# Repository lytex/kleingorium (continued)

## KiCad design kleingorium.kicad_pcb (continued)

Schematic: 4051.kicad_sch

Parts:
C20: 100nF; C_0805_2012Metric
R34, R35, R36, R37: 100k; R_0805_2012Metric
U12: 4051; SOIC-16_3.9x9.9mm_P1.27mm

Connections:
/Bottom plate/4051/A: R35.1, U12.11 (A); also elsewhere on the board
/Bottom plate/4051/B: R36.1, U12.10 (B); also elsewhere on the board
/Bottom plate/4051/C: R37.1, U12.9 (C); also elsewhere on the board
/Bottom plate/4051/Inhibit: R34.1, U12.6 (Inh); also elsewhere on the board
/Bottom plate/4051/X: U12.3 (X)
/Bottom plate/4051/X0: U12.13 (X0); also elsewhere on the board
/Bottom plate/4051/X1: U12.14 (X1); also elsewhere on the board
/Bottom plate/4051/X2: U12.15 (X2); also elsewhere on the board
/Bottom plate/4051/X3: U12.12 (X3); also elsewhere on the board
/Bottom plate/4051/X4: U12.1 (X4); also elsewhere on the board
/Bottom plate/4051/X5: U12.5 (X5); also elsewhere on the board
/Bottom plate/4051/X6: U12.2 (X6); also elsewhere on the board
/Bottom plate/4051/X7: U12.4 (X7); also elsewhere on the board
GND2: C20.2, R34.2, R35.2, R36.2, R37.2, U12.7 (VEE), U12.8 (VSS); also elsewhere on the board
VDDF: C20.1, U12.16 (VDD); also elsewhere on the board

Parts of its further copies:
C22: 100nF; C_0805_2012Metric
R38, R39, R40, R41: 100k; R_0805_2012Metric
U13: 4051; SOIC-16_3.9x9.9mm_P1.27mm

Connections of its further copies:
/Bottom plate/4051 2/A: R39.1, U13.11 (A); also elsewhere on the board
/Bottom plate/4051 2/B: R40.1, U13.10 (B); also elsewhere on the board
/Bottom plate/4051 2/C: R41.1, U13.9 (C); also elsewhere on the board
/Bottom plate/4051 2/Inhibit: R38.1, U13.6 (Inh); also elsewhere on the board
/Bottom plate/4051 2/X: U13.3 (X); also elsewhere on the board
/Bottom plate/4051 2/X0: U13.13 (X0); also elsewhere on the board
/Bottom plate/4051 2/X1: U13.14 (X1); also elsewhere on the board
/Bottom plate/4051 2/X2: U13.15 (X2); also elsewhere on the board
/Bottom plate/4051 2/X3: U13.12 (X3); also elsewhere on the board
/Bottom plate/4051 2/X4: U13.1 (X4); also elsewhere on the board
/Bottom plate/4051 2/X5: U13.5 (X5); also elsewhere on the board
/Bottom plate/4051 2/X6: U13.2 (X6); also elsewhere on the board
/Bottom plate/4051 2/X7: U13.4 (X7); also elsewhere on the board
GND2: C22.2, R38.2, R39.2, R40.2, R41.2, U13.7 (VEE), U13.8 (VSS); also elsewhere on the board
VDDF: C22.1, U13.16 (VDD); also elsewhere on the board

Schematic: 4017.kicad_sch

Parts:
R24, R25, R26: 100K; R_0805_2012Metric
U8: 4017; SOIC-16_3.9x9.9mm_P1.27mm

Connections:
/Multiplier-Divider/upper half/4017/Clock: R24.1, U8.14 (CLK); also elsewhere on the board
/Multiplier-Divider/upper half/4017/ClockEnable: R25.1, U8.13 (CKEN)
/Multiplier-Divider/upper half/4017/Q0: U8.3 (Q0); also elsewhere on the board
/Multiplier-Divider/upper half/4017/Q1: U8.2 (Q1); also elsewhere on the board
/Multiplier-Divider/upper half/4017/Q2: U8.4 (Q2); also elsewhere on the board
/Multiplier-Divider/upper half/4017/Q3: U8.7 (Q3); also elsewhere on the board
/Multiplier-Divider/upper half/4017/Q4: U8.10 (Q4); also elsewhere on the board
/Multiplier-Divider/upper half/4017/Q5: U8.1 (Q5); also elsewhere on the board
/Multiplier-Divider/upper half/4017/Q6: U8.5 (Q6); also elsewhere on the board
/Multiplier-Divider/upper half/4017/Q7: U8.6 (Q7); also elsewhere on the board
/Multiplier-Divider/upper half/4017/Q8: U8.9 (Q8); also elsewhere on the board
/Multiplier-Divider/upper half/4017/Q9: U8.11 (Q9); also elsewhere on the board
/Multiplier-Divider/upper half/4017/Reset: R26.1, U8.15 (Reset); also elsewhere on the board
GND: R24.2, R25.2, R26.2, U8.8 (VSS); also elsewhere on the board
VCC: U8.16 (VDD); also elsewhere on the board

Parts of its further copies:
R2, R3, R4: 100K; R_0805_2012Metric
U1: 4017; SOIC-16_3.9x9.9mm_P1.27mm

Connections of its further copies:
/Multiplier-Divider/lower half/4017/Clock: R2.1, U1.14 (CLK); also elsewhere on the board
/Multiplier-Divider/lower half/4017/ClockEnable: R3.1, U1.13 (CKEN)
/Multiplier-Divider/lower half/4017/Q0: U1.3 (Q0); also elsewhere on the board
/Multiplier-Divider/lower half/4017/Q1: U1.2 (Q1); also elsewhere on the board
/Multiplier-Divider/lower half/4017/Q2: U1.4 (Q2); also elsewhere on the board
/Multiplier-Divider/lower half/4017/Q3: U1.7 (Q3); also elsewhere on the board
/Multiplier-Divider/lower half/4017/Q4: U1.10 (Q4); also elsewhere on the board
/Multiplier-Divider/lower half/4017/Q5: U1.1 (Q5); also elsewhere on the board
/Multiplier-Divider/lower half/4017/Q6: U1.5 (Q6); also elsewhere on the board
/Multiplier-Divider/lower half/4017/Q7: U1.6 (Q7); also elsewhere on the board
/Multiplier-Divider/lower half/4017/Q8: U1.9 (Q8); also elsewhere on the board
/Multiplier-Divider/lower half/4017/Q9: U1.11 (Q9); also elsewhere on the board
/Multiplier-Divider/lower half/4017/Reset: R4.1, U1.15 (Reset); also elsewhere on the board
GND: R2.2, R3.2, R4.2, U1.8 (VSS); also elsewhere on the board
VCC: U1.16 (VDD); also elsewhere on the board

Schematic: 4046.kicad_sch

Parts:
C4, C6: 1uF; C_0805_2012Metric
C5: 1nF; C_0805_2012Metric
C25: 10nF; C_0805_2012Metric
R27, R28: 100K; R_0805_2012Metric
R29, R30: 100k; Potentiometer_Alps_RK097_Single_Horizontal
RV2: 2K; Potentiometer_Bourns_3296Z_Horizontal
SW6: PLL Type; SW_Slide_SPDT_Straight_CK_OS102011MS2Q
SW9: SW_DPDT_x2; SW_CK_JS202011CQN_DPDT_Straight
U9: 4046; SOIC-16_3.9x9.9mm_P1.27mm

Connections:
/Multiplier-Divider/upper half/4017/Clock: U9.4 (FOUT); also elsewhere on the board
/Multiplier-Divider/upper half/4046/Comp: U9.3 (RefIn); also elsewhere on the board
/Multiplier-Divider/upper half/4046/Inh: R28.1, U9.5 (Inh); also elsewhere on the board
/Multiplier-Divider/upper half/4046/SigIn: C4.2, RV2.1, RV2.2; also elsewhere on the board
GND: C6.1, R27.2, R28.2, RV2.3, U9.8 (VSS); also elsewhere on the board
unnamed: C6.2, R30.2, R30.3
unnamed: SW6.1 (A), U9.2 (PC1)
unnamed: R29.1, SW6.2 (B)
unnamed: SW6.3 (C), U9.13 (PC2)
unnamed: C25.1, SW9.1 (A)
unnamed: SW9.2 (B), U9.6 (C1)
unnamed: SW9.5 (B), U9.7 (C2)
unnamed: C25.2, SW9.6 (C)
unnamed: R27.1, U9.11 (R1)
unnamed: C4.1, U9.14 (SigIn)
unnamed: R29.2, R29.3, R30.1, U9.9 (VCOin)
VCC: U9.16 (VDD); also elsewhere on the board

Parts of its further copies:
C1, C3: 1uF; C_0805_2012Metric
C28: 1nF; C_0805_2012Metric
C29: 10nF; C_0805_2012Metric
R7, R8: 100K; R_0805_2012Metric
R9, R10: 100k; Potentiometer_Alps_RK097_Single_Horizontal
RV1: 2K; Potentiometer_Bourns_3296Z_Horizontal
SW2: PLL Type; SW_Slide_SPDT_Straight_CK_OS102011MS2Q
SW10: SW_DPDT_x2; SW_CK_JS202011CQN_DPDT_Straight
U3: 4046; SOIC-16_3.9x9.9mm_P1.27mm

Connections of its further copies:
/Multiplier-Divider/lower half/4017/Clock: U3.4 (FOUT); also elsewhere on the board
/Multiplier-Divider/lower half/4046/Comp: U3.3 (RefIn); also elsewhere on the board
/Multiplier-Divider/lower half/4046/Inh: R8.1, U3.5 (Inh); also elsewhere on the board
/Multiplier-Divider/lower half/4046/SigIn: C1.2, RV1.1, RV1.2; also elsewhere on the board
GND: C3.1, R7.2, R8.2, RV1.3, U3.8 (VSS); also elsewhere on the board
unnamed: C3.2, R10.2, R10.3
unnamed: SW2.1 (A), U3.2 (PC1)
unnamed: R9.1, SW2.2 (B)
unnamed: SW2.3 (C), U3.13 (PC2)
unnamed: C29.1, SW10.1 (A)
unnamed: SW10.2 (B), U3.6 (C1)
unnamed: C28.1, SW10.3 (C)
unnamed: C28.2, SW10.4 (A)
unnamed: SW10.5 (B), U3.7 (C2)
unnamed: C29.2, SW10.6 (C)
unnamed: R7.1, U3.11 (R1)
unnamed: C1.1, U3.14 (SigIn)
unnamed: R9.2, R9.3, R10.1, U3.9 (VCOin)
VCC: U3.16 (VDD); also elsewhere on the board

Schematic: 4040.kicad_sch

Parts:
R23: 100K; R_0805_2012Metric
U7: 4040; SOIC-16_3.9x9.9mm_P1.27mm

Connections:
/Multiplier-Divider/upper half/4017/Clock: U7.10 (CLK); also elsewhere on the board
/Multiplier-Divider/upper half/4040/Q0: U7.9 (Q0); also elsewhere on the board
/Multiplier-Divider/upper half/4040/Q1: U7.7 (Q1); also elsewhere on the board
/Multiplier-Divider/upper half/4040/Q2: U7.6 (Q2); also elsewhere on the board
/Multiplier-Divider/upper half/4040/Q3: U7.5 (Q3); also elsewhere on the board
/Multiplier-Divider/upper half/4040/Q4: U7.3 (Q4); also elsewhere on the board
/Multiplier-Divider/upper half/4040/Q5: U7.2 (Q5); also elsewhere on the board
/Multiplier-Divider/upper half/4040/Q6: U7.4 (Q6); also elsewhere on the board
/Multiplier-Divider/upper half/4040/Q7: U7.13 (Q7); also elsewhere on the board
/Multiplier-Divider/upper half/4040/Q8: U7.12 (Q8); also elsewhere on the board
/Multiplier-Divider/upper half/4040/Q9: U7.14 (Q9); also elsewhere on the board
/Multiplier-Divider/upper half/4040/Q10: U7.15 (Q10); also elsewhere on the board
/Multiplier-Divider/upper half/4040/Q11: U7.1 (Q11); also elsewhere on the board
/Multiplier-Divider/upper half/4040/Reset: R23.1, U7.11 (Reset); also elsewhere on the board
GND: R23.2, U7.8 (VSS); also elsewhere on the board
VCC: U7.16 (VDD); also elsewhere on the board

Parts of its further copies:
R5: 100K; R_0805_2012Metric
U2: 4040; SOIC-16_3.9x9.9mm_P1.27mm

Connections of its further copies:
/Multiplier-Divider/lower half/4017/Clock: U2.10 (CLK); also elsewhere on the board
/Multiplier-Divider/lower half/4040/Q0: U2.9 (Q0)
/Multiplier-Divider/lower half/4040/Q1: U2.7 (Q1); also elsewhere on the board
/Multiplier-Divider/lower half/4040/Q2: U2.6 (Q2)
/Multiplier-Divider/lower half/4040/Q3: U2.5 (Q3); also elsewhere on the board
/Multiplier-Divider/lower half/4040/Q4: U2.3 (Q4)
/Multiplier-Divider/lower half/4040/Q5: U2.2 (Q5)
/Multiplier-Divider/lower half/4040/Q6: U2.4 (Q6)
/Multiplier-Divider/lower half/4040/Q7: U2.13 (Q7)
/Multiplier-Divider/lower half/4040/Q8: U2.12 (Q8)
/Multiplier-Divider/lower half/4040/Q9: U2.14 (Q9)
/Multiplier-Divider/lower half/4040/Q10: U2.15 (Q10)
/Multiplier-Divider/lower half/4040/Q11: U2.1 (Q11)
/Multiplier-Divider/lower half/4040/Reset: R5.1, U2.11 (Reset); also elsewhere on the board
GND: R5.2, U2.8 (VSS); also elsewhere on the board
VCC: U2.16 (VDD); also elsewhere on the board

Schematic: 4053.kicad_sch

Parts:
R20, R21, R22: 100K; R_0805_2012Metric
U6: CD4053B; SOIC-16_3.9x9.9mm_P1.27mm

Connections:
/Multiplier-Divider/4520/CKB: U6.14 (A); also elsewhere on the board
/Multiplier-Divider/upper half/4040/Q1: U6.13 (A1); also elsewhere on the board
/Multiplier-Divider/upper half/4040/Q3: U6.2 (B0); also elsewhere on the board
/Multiplier-Divider/upper half/4053/A0: U6.1 (B1), U6.12 (A0); also elsewhere on the board
/Multiplier-Divider/upper half/4053/B: U6.15 (B); also elsewhere on the board
/Multiplier-Divider/upper half/4053/C: U6.4 (C); also elsewhere on the board
/Multiplier-Divider/upper half/4053/C0: U6.5 (C0); also elsewhere on the board
/Multiplier-Divider/upper half/4053/C1: U6.3 (C1); also elsewhere on the board
/Multiplier-Divider/upper half/4053/S3: R21.1, U6.9 (S3); also elsewhere on the board
/Multiplier-Divider/upper half/4053/Select: R20.1, U6.10 (S2), U6.11 (S1); also elsewhere on the board
GND: R20.2, R21.2, R22.2, U6.7 (VEE), U6.8 (VSS); also elsewhere on the board
unnamed: R22.1, U6.6 (INH)
VCC: U6.16 (VDD); also elsewhere on the board

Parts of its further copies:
R11, R12, R19: 100K; R_0805_2012Metric
U5: CD4053B; SOIC-16_3.9x9.9mm_P1.27mm

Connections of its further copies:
/Multiplier-Divider/4520/CKA: U5.14 (A); also elsewhere on the board
/Multiplier-Divider/lower half/4040/Q1: U5.13 (A1); also elsewhere on the board
/Multiplier-Divider/lower half/4040/Q3: U5.2 (B0); also elsewhere on the board
/Multiplier-Divider/lower half/4053/A0: U5.1 (B1), U5.12 (A0); also elsewhere on the board
/Multiplier-Divider/lower half/4053/B: U5.15 (B); also elsewhere on the board
/Multiplier-Divider/lower half/4053/C: U5.4 (C); also elsewhere on the board
/Multiplier-Divider/lower half/4053/C0: U5.5 (C0); also elsewhere on the board
/Multiplier-Divider/lower half/4053/C1: U5.3 (C1); also elsewhere on the board
/Multiplier-Divider/lower half/4053/S3: R12.1, U5.9 (S3); also elsewhere on the board
/Multiplier-Divider/lower half/4053/Select: R11.1, U5.10 (S2), U5.11 (S1); also elsewhere on the board
GND: R11.2, R12.2, R19.2, U5.7 (VEE), U5.8 (VSS); also elsewhere on the board
unnamed: R19.1, U5.6 (INH)
VCC: U5.16 (VDD); also elsewhere on the board

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
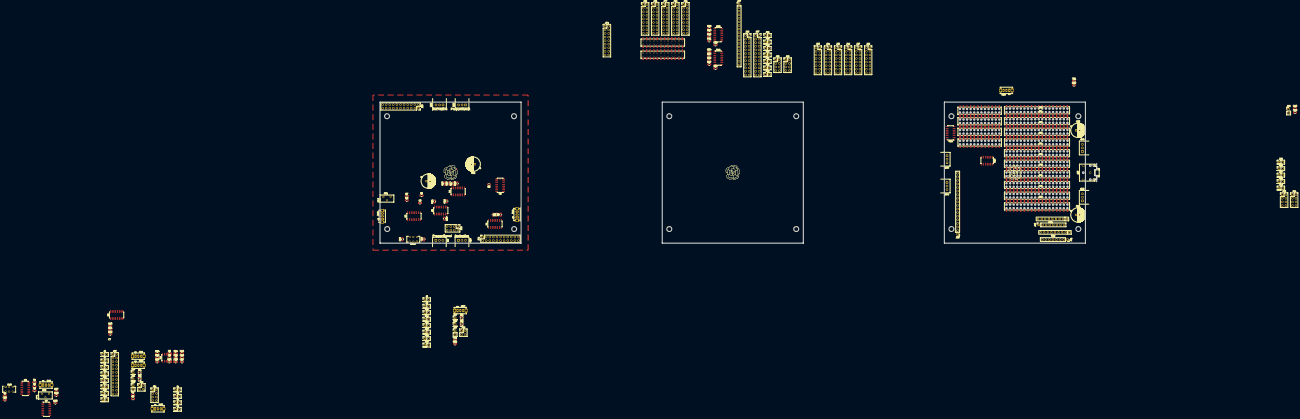
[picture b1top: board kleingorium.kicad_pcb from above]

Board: 2 copper layers, 186 parts (0 on the bottom side), 287 nets.

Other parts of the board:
C5#2: 1nF; C_0805_2012Metric
J27: 4040 Output; PinHeader_2x12_P2.54mm_Vertical
J43, J44, J45, J46, J47, J64: Conn_02x08_Odd_Even; PinSocket_2x08_P2.54mm_Vertical

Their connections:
/Bottom plate/4051 2/A: J43.9, J43.10, J44.9, J44.10, J45.9, J45.10, J46.9, J46.10, J47.9, J47.10, J64.9, J64.10; also elsewhere on the board
/Bottom plate/4051 2/B: J43.11, J43.12, J44.11, J44.12, J45.11, J45.12, J46.11, J46.12, J47.11, J47.12, J64.11, J64.12; also elsewhere on the board
/Bottom plate/4051 2/C: J43.13, J43.14, J44.13, J44.14, J45.13, J45.14, J46.13, J46.14, J47.13, J47.14, J64.13, J64.14; also elsewhere on the board
/Bottom plate/4051/A: J43.1, J43.2, J44.1, J44.2, J45.1, J45.2, J46.1, J46.2, J47.1, J47.2, J64.1, J64.2; also elsewhere on the board
/Bottom plate/4051/B: J43.3, J43.4, J44.3, J44.4, J45.3, J45.4, J46.3, J46.4, J47.3, J47.4, J64.3, J64.4; also elsewhere on the board
/Bottom plate/4051/C: J43.5, J43.6, J44.5, J44.6, J45.5, J45.6, J46.5, J46.6, J47.5, J47.6, J64.5, J64.6; also elsewhere on the board
/Multiplier-Divider/upper half/4040/Q0: J27.1, J27.2; also elsewhere on the board
/Multiplier-Divider/upper half/4040/Q1: J27.3, J27.4; also elsewhere on the board
/Multiplier-Divider/upper half/4040/Q2: J27.5, J27.6; also elsewhere on the board
/Multiplier-Divider/upper half/4040/Q3: J27.7, J27.8; also elsewhere on the board
/Multiplier-Divider/upper half/4040/Q4: J27.9, J27.10; also elsewhere on the board
/Multiplier-Divider/upper half/4040/Q5: J27.11, J27.12; also elsewhere on the board
/Multiplier-Divider/upper half/4040/Q6: J27.13, J27.14; also elsewhere on the board
/Multiplier-Divider/upper half/4040/Q7: J27.15, J27.16; also elsewhere on the board
/Multiplier-Divider/upper half/4040/Q8: J27.17, J27.18; also elsewhere on the board
/Multiplier-Divider/upper half/4040/Q9: J27.19, J27.20; also elsewhere on the board
/Multiplier-Divider/upper half/4040/Q10: J27.21, J27.22; also elsewhere on the board
/Multiplier-Divider/upper half/4040/Q11: J27.23, J27.24; also elsewhere on the board
unnamed: J43.7, J43.8, J44.7, J44.8, J45.7, J45.8, J46.7, J46.8, J47.7, J47.8, J64.7, J64.8
unnamed: J43.15, J43.16, J44.15, J44.16, J45.15, J45.16, J46.15, J46.16, J47.15, J47.16, J64.15, J64.16

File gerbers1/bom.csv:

Comment,Designator,Footprint,LCSC
VCC,"J1,J2",Connector_PinHeader_2.54mm:PinHeader_2x01_P2.54mm_Vertical,
GND,"J3,J4",Connector_PinHeader_2.54mm:PinHeader_2x01_P2.54mm_Vertical,
100nF,"C8,C9,C10,C11,C12,C13,C14,C16,C17",Capacitor_THT:C_Disc_D3.0mm_W1.6mm_P2.50mm,
10uF,"C7,C15",Capacitor_THT:CP_Radial_D5.0mm_P2.50mm,
Output,"J31,J32",Connector_PinHeader_2.54mm:PinHeader_2x04_P2.54mm_Vertical,
1uF,"C1,C4",Capacitor_THT:C_Disc_D4.3mm_W1.9mm_P5.00mm,
4040,"U2,U7",Package_DIP:DIP-16_W7.62mm,
100K,"R2,R3,R4,R5,R7,R8,R11,R12,R15,R16,R17,R18,R19,R20,R21,R22,R23,R24,R25,R26,R27,R28",Resistor_THT:R_Axial_DIN0207_L6.3mm_D2.5mm_P10.16mm_Horizontal,
Chain,SW5,Button_Switch_THT:SW_E-Switch_EG1271_SPDT,
4520,U4,Package_DIP:DIP-16_W7.62mm,
4017 Fdbk,"J29,J30",Connector_PinHeader_2.54mm:PinHeader_2x01_P2.54mm_Vertical,
4046 CompIn,"SW1,SW7",Button_Switch_THT:SW_E-Switch_EG1271_SPDT,
4046 Comp In,"J15,J16",Connector_PinHeader_2.54mm:PinHeader_2x01_P2.54mm_Vertical,
4017 Pins,"J33,J34",Connector_PinSocket_2.54mm:PinSocket_2x11_P2.54mm_Vertical,
Select,"J11,J12",Connector_PinHeader_2.54mm:PinHeader_2x01_P2.54mm_Vertical,
4046 Comp,"J8,J10",Connector_PinHeader_2.54mm:PinHeader_2x01_P2.54mm_Vertical,
2N3904,"Q1,Q2,Q3,Q4",Package_TO_SOT_THT:TO-92_Inline_Wide,
4053 C,"J23,J24",Connector_PinHeader_2.54mm:PinHeader_2x01_P2.54mm_Vertical,
Inh,"J13,J14",Connector_PinHeader_2.54mm:PinHeader_1x01_P2.54mm_Vertical,
100k,"R1,R6,R31,R32",Resistor_THT:R_Axial_DIN0207_L6.3mm_D2.5mm_P10.16mm_Horizontal,
4040 Input,"J19,J20",Connector_PinHeader_2.54mm:PinHeader_1x02_P2.54mm_Vertical,
4017 Feedback,"SW3,SW4",Button_Switch_THT:SW_CK_JS202011CQN_DPDT_Straight,
4040 Output,"J27,J28",Connector_PinHeader_2.54mm:PinHeader_2x12_P2.54mm_Vertical,
Input,"J5,J6",Connector_PinHeader_2.54mm:PinHeader_2x01_P2.54mm_Vertical,
4053 C0 C1,"J25,J26",Connector_PinHeader_2.54mm:PinHeader_2x02_P2.54mm_Vertical,
4046 Out,"J17,J18",Connector_PinHeader_2.54mm:PinHeader_2x01_P2.54mm_Vertical,
4053 S3,"J21,J22",Connector_PinHeader_2.54mm:PinHeader_1x01_P2.54mm_Vertical,
4046 SigIn,"J7,J9",Connector_PinHeader_2.54mm:PinHeader_2x01_P2.54mm_Vertical,
4017,"U1,U8",Package_DIP:DIP-16_W7.62mm,
PLL Type,"SW2,SW6",Button_Switch_THT:SW_E-Switch_EG1271_SPDT,
4046,"U3,U9",Package_DIP:DIP-16_W7.62mm,
100k,"R9,R10,R29,R30",Potentiometer_THT:Potentiometer_Alps_RK097_Single_Horizontal,
1uF,"C3,C6",Capacitor_THT:C_Disc_D5.0mm_W2.5mm_P5.00mm,
C1,"C2,C5",Capacitor_THT:C_Disc_D4.3mm_W1.9mm_P5.00mm,
2K,"RV1,RV2",Potentiometer_THT:Potentiometer_Bourns_3296W_Vertical,
CD4053B,"U5,U6",Package_DIP:DIP-16_W7.62mm,

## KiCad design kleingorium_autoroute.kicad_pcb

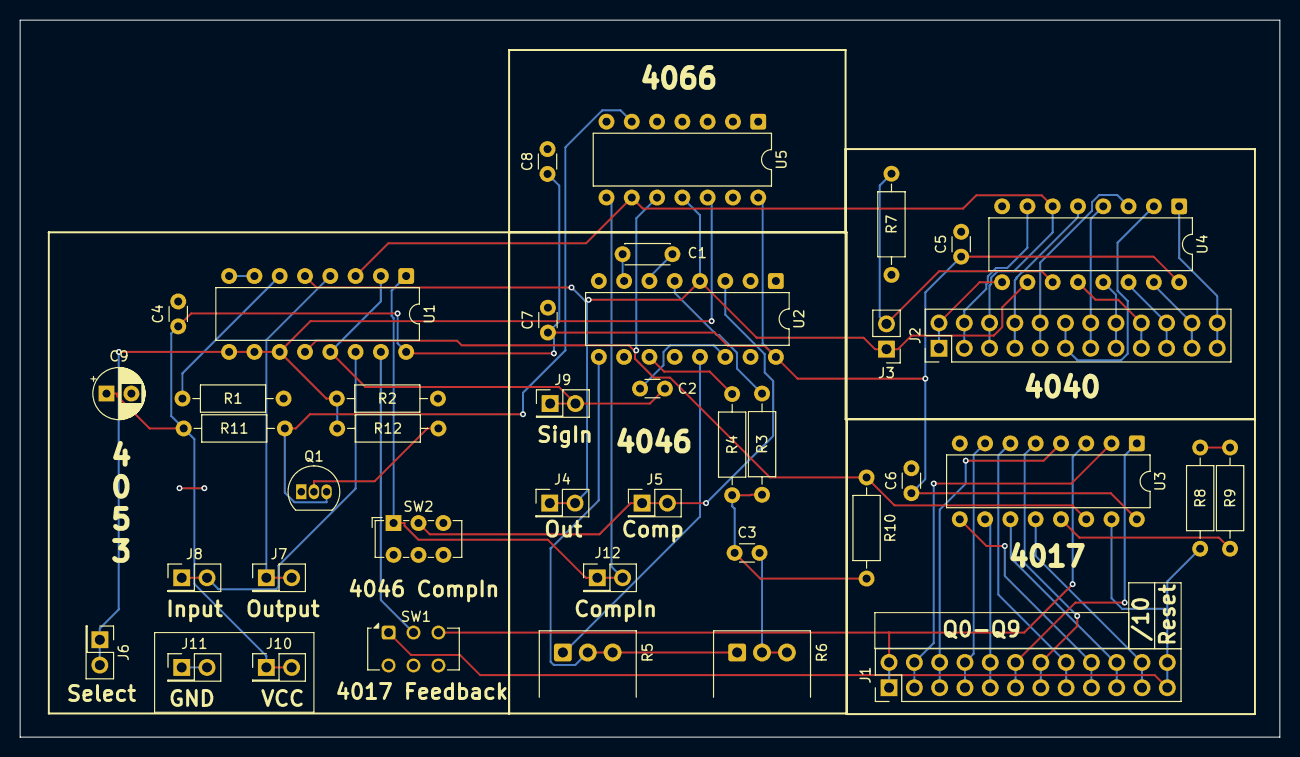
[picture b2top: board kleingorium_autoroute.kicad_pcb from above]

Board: 2 copper layers, 126.5 x 72.0 mm, 41 parts (0 on the bottom side), 48 nets.

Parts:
C1: C1; C_Disc_D4.3mm_W1.9mm_P5.00mm
C2, C3: 1uF; C_Disc_D3.0mm_W1.6mm_P2.50mm
C4, C5, C6, C7, C8: 100nF; C_Disc_D3.0mm_W1.6mm_P2.50mm
C9: 10uF; CP_Radial_D5.0mm_P2.50mm
J1: 4017 Pins; PinHeader_2x12_P2.54mm_Vertical
J2: 4040 Output; PinHeader_2x12_P2.54mm_Vertical
J3: 4040 Input; PinHeader_1x02_P2.54mm_Vertical
J4: 4046 Out; PinHeader_2x01_P2.54mm_Vertical
J5: 4046 Comp; PinHeader_2x01_P2.54mm_Vertical
J6: Select; PinHeader_2x01_P2.54mm_Vertical
J7: Output; PinHeader_2x01_P2.54mm_Vertical
J8: Input; PinHeader_2x01_P2.54mm_Vertical
J9: 4046 SigIn; PinHeader_2x01_P2.54mm_Vertical
J10: VCC; PinHeader_2x01_P2.54mm_Vertical
J11: GND; PinHeader_2x01_P2.54mm_Vertical
J12: 4046 Comp In; PinHeader_2x01_P2.54mm_Vertical
Q1: 2N3904; TO-92_Inline
R1, R2, R3, R4, R7, R8, R9, R10: 100K; R_Axial_DIN0207_L6.3mm_D2.5mm_P10.16mm_Horizontal
R5: R5; Potentiometer_Alps_RK097_Single_Horizontal
R6: R6; Potentiometer_Alps_RK097_Single_Horizontal
R11: 10k; R_Axial_DIN0207_L6.3mm_D2.5mm_P10.16mm_Horizontal
R12: 100k; R_Axial_DIN0207_L6.3mm_D2.5mm_P10.16mm_Horizontal
SW1: 4017 Feedback; SW_CK_JS202011CQN_DPDT_Straight
SW2: 4046 CompIn; SW_E-Switch_EG1271_SPDT
U1: CD4053B; DIP-16_W7.62mm
U2: 4046; DIP-16_W7.62mm
U3: 4017; DIP-16_W7.62mm
U4: 4040; DIP-16_W7.62mm
U5: CD4066BE; DIP-14_W7.62mm

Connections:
/4017/Clock: R10.1, U1.12 (A0), U3.14 (CLK), U5.10
/4017/ClockEnable: R9.1, U3.13 (CKEN)
/4017/Q0: J1.1, J1.2, SW1.3 (C), U3.3 (Q0)
/4017/Q1: J1.3, J1.4, U3.2 (Q1)
/4017/Q2: J1.5, J1.6, U3.4 (Q2)
/4017/Q3: J1.7, J1.8, U3.7 (Q3)
/4017/Q4: J1.9, J1.10, U3.10 (Q4)
/4017/Q5: J1.11, J1.12, U3.1 (Q5)
/4017/Q6: J1.13, J1.14, U3.5 (Q6)
/4017/Q7: J1.15, J1.16, U3.6 (Q7)
/4017/Q8: J1.17, J1.18, U3.9 (Q8)
/4017/Q9: J1.19, J1.20, U3.11 (Q9)
/4017/Q10: J1.21, J1.22, U3.12 (Cout)
/4017/Reset: J1.23, J1.24, R8.1, SW1.1 (A), U3.15 (Reset)
/4040/Clock: J3.1, J4.1, J4.2, U1.5 (C0), U2.4 (FOUT), U4.10 (CLK), U5.11
/4040/Q0: J2.1, J2.2, U4.9 (Q0)
/4040/Q1: J2.3, J2.4, U4.7 (Q1)
/4040/Q2: J2.5, J2.6, U1.3 (C1), U4.6 (Q2), U5.9
/4040/Q3: J2.7, J2.8, U4.5 (Q3)
/4040/Q4: J2.9, J2.10, U4.3 (Q4)
/4040/Q5: J2.11, J2.12, U4.2 (Q5)
/4040/Q6: J2.13, J2.14, U4.4 (Q6)
/4040/Q7: J2.15, J2.16, U4.13 (Q7)
/4040/Q8: J2.17, J2.18, U4.12 (Q8)
/4040/Q9: J2.19, J2.20, U4.14 (Q9)
/4040/Q10: J2.21, J2.22, U4.15 (Q10)
/4040/Q11: J2.23, J2.24, U4.1 (Q11)
/4040/Reset: J3.2, R7.1, U4.11 (Reset)
/4046/Comp: J5.1, J5.2, SW2.2 (B), U2.3 (RefIn)
/4046/SigIn: C2.2, J9.1, J9.2, U1.2 (B0), U1.13 (A1)
/4053/A: J8.1, J8.2, U1.14 (A)
/4053/B: SW1.2 (B), U1.15 (B)
/4053/B1: J12.1, J12.2, SW2.1 (A), U1.1 (B1), U5.8
/4053/C: J7.1, J7.2, U1.4 (C)
/4053/Select: J6.1, J6.2, R2.1, R12.1, U1.9 (S3), U1.10 (S2), U1.11 (S1), U5.12
/4066/Cen: Q1.3 (C), R11.2, U5.6
GND: C3.1, C4.2, C5.2, C6.2, C7.2, C8.2, C9.2, J11.1, J11.2, Q1.1 (E), R1.2, R2.2, R3.2, R4.2, R7.2, R8.2, R9.2, R10.2, U1.7 (VEE), U1.8 (VSS), U2.8 (VSS), U3.8 (VSS), U4.8 (VSS), U5.7 (V_{SS})
unnamed: C3.2, R6.2, R6.3
unnamed: Q1.2 (B), R12.2
unnamed: R1.1, U1.6 (INH)
unnamed: C1.1, U2.6 (C1)
unnamed: C1.2, U2.7 (C2)
unnamed: R3.1, U2.5 (Inh)
unnamed: R5.1, U2.13 (PC2)
unnamed: R4.1, U2.11 (R1)
unnamed: C2.1, U2.14 (SigIn)
unnamed: R5.2, R5.3, R6.1, U2.9 (VCOin)
VCC: C4.1, C5.1, C6.1, C7.1, C8.1, C9.1, J10.1, J10.2, R11.1, U1.16 (VDD), U2.16 (VDD), U3.16 (VDD), U4.16 (VDD), U5.14 (V_{DD})

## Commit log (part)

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2025-05-12 remove lock
2025-05-12 some cleanup
2025-05-12 renaming
2025-05-12 before main routing
2025-05-12 after main routing
2025-05-12 after fixing errors
2025-05-12 fix errors
2025-05-13 schematic doubling without pcb placing
2025-05-13 pcb placing doubling without routing
2025-05-15 final version v1
2025-05-15 final version v2
2025-06-10 final commit
2025-06-10 move into new folder
2025-06-14 fix errors with 4066 and Select
2025-06-14 export ibom
2025-06-14 generate gerbers
2025-06-14 commit backups
2025-06-14 remove gerber files in root path
2025-06-14 change order of feedback buttons
2025-06-14 update gerbers
2025-06-14 remove .lck and autosave files
2025-06-16 remove zip files and older versions
2025-06-16 gitignore removed files
2025-06-16 change potentiometer legs R5 and R33
2025-06-16 remove pull down resistor, change pull up from 10k to 2.2k
2025-06-17 add explanative text and JLCJLCJLCJLC marker
2025-06-20 add schematics
2025-06-22 remove duplicated schematics
2025-06-22 add Select transistor
2025-06-22 add feedback design
2025-06-22 Revert "add feedback design"
    This reverts commit 3c7214ef6395e47e9ac3d60155079abb95354c45.
2025-06-22 add pull-down to A1, remove Q0 pull up
2025-06-23 change potentiometer legs R5 and R33 again
2025-06-23 silkscreen adjusments, make RVx text bigger
2025-07-03 add final gerbers
2025-07-17 new ibom
2025-07-19 fix transistor circuit issue
2025-08-02 add calculator script in python
2025-08-09 remove RV3,4 and change RV1,2 to 2k
2025-08-16 add Inhibit 4046
2025-08-16 cleanup
2025-08-22 add cent calculator with colormap
2025-08-26 kleingorium scale new version
2025-09-25 v1.2
2025-10-07 add arduino scripts
2025-10-12 new ibom v1.2
2026-01-25 add missing via
2026-03-20 v2 initial commit
2026-03-20 schematic finished
2026-03-20 wip symmetric layout
2026-03-20 placed components
2026-03-21 two halves routing
2026-03-21 two layer pcb
2026-03-21 wip assemblying everything
2026-03-21 wip assemblying everything 2
2026-03-21 3 board alignment
2026-03-23 full alignment
2026-03-23 bottom plate routed
2026-03-24 add 4040 Clk Rst connector
2026-04-08 almost routed
2026-04-09 everything routed
2026-04-09 everything routed 2
2026-04-09 thermal improvements
2026-04-09 remove conflicts
2026-04-20 more silkscreen, minor circuits adjustments for text
2026-04-20 fix alignment issues
2026-04-20 more silkscreen
2026-04-21 18x20 design
2026-04-22 last commit before gerbers
2026-04-22 fix back silkscreen
2026-04-22 fix board
2026-04-22 add version silkscreen
2026-04-25 add power specs
